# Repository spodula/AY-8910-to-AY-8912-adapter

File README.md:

# AY-8910-to-AY-8912-adapter
PCB to adapt an AY-3-8912 footprint to an AY-3-8910 chip

This project was done for my Superfo Harlequin 128 build because the cost of an AY-3-8912 is substantially more
than an AY-3-8910 despite the latter being much more functional. Even taking into account PCB manafacturing costs. 

If you want a PCB, The Gerber folder can just be zipped up and sent straight to your preferred PCB manafacturer.

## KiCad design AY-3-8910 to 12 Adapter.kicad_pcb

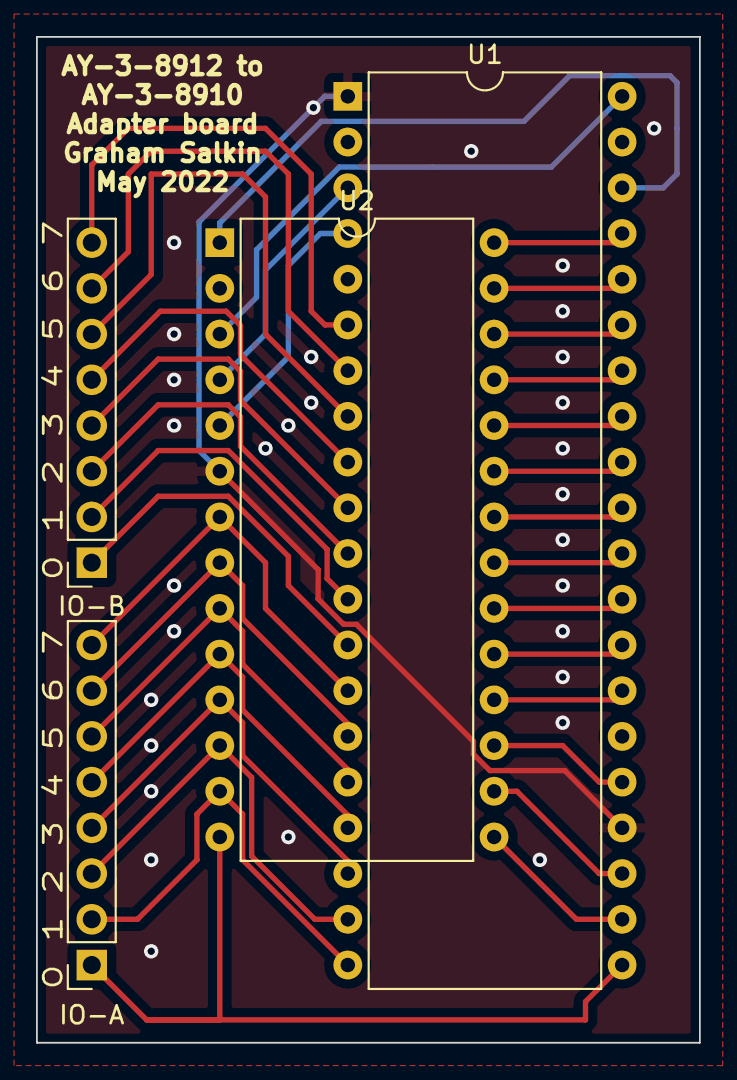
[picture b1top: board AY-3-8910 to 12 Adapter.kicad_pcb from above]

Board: 2 copper layers, 36.8 x 55.9 mm, 4 parts (0 on the bottom side), 35 nets.

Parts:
IO-A: 0 1 2 3 4 5 6 7; PinSocket_1x08_P2.54mm_Vertical
IO-B: 0 1 2 3 4 5 6 7; PinSocket_1x08_P2.54mm_Vertical
U1: AY-3-8910; DIP-40_W15.24mm
U2: AY-3-8912; DIP-28_W15.24mm

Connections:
GND: U1.1 (Vss), U1.24 (/A9), U2.6 (Vss)
unnamed: IO-B.1, U1.13 (IOB0)
unnamed: IO-B.2, U1.12 (IOB1)
unnamed: IO-B.3, U1.11 (IOB2)
unnamed: IO-B.4, U1.10 (IOB3)
unnamed: IO-B.5, U1.9 (IOB4)
unnamed: IO-B.6, U1.8 (IOB5)
unnamed: IO-B.7, U1.7 (IOB6)
unnamed: IO-B.8, U1.6 (IOB7)
unnamed: IO-A.1, U1.21 (IOA0), U2.14 (IOA0)
unnamed: IO-A.2, U1.20 (IOA1), U2.13 (IOA1)
unnamed: IO-A.3, U1.19 (IOA2), U2.12 (IOA2)
unnamed: IO-A.4, U1.18 (IOA3), U2.11 (IOA3)
unnamed: IO-A.5, U1.17 (IOA4), U2.10 (IOA4)
unnamed: IO-A.6, U1.16 (IOA5), U2.9 (IOA5)
unnamed: IO-A.7, U1.15 (IOA6), U2.8 (IOA6)
unnamed: IO-A.8, U1.14 (IOA7), U2.7 (IOA7)
unnamed: U1.3 (Analog_B), U2.4 (Analog_B)
unnamed: U1.4 (Analog_A), U2.5 (Analog_A)
unnamed: U1.22 (CLOCK), U2.15 (CLOCK)
unnamed: U1.23 (/RESET), U2.16 (/RESET)
unnamed: U1.25 (A8), U2.17 (A8)
unnamed: U1.27 (BDIR), U2.18 (BDIR)
unnamed: U1.28 (BC2), U2.19 (BC2)
unnamed: U1.29 (BC1), U2.20 (BC1)
unnamed: U1.30 (DA7), U2.21 (DA7)
unnamed: U1.31 (DA6), U2.22 (DA6)
unnamed: U1.32 (DA5), U2.23 (DA5)
unnamed: U1.33 (DA4), U2.24 (DA4)
unnamed: U1.34 (DA3), U2.25 (DA3)
unnamed: U1.35 (DA2), U2.26 (DA2)
unnamed: U1.36 (DA1), U2.27 (DA1)
unnamed: U1.37 (DA0), U2.28 (DA0)
unnamed: U1.38 (Analog_C), U2.1 (Analog_C)
unnamed: U1.40 (Vcc), U2.3 (Vcc)

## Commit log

2022-05-25 Added AY symbol library for completeness
2022-05-25 Fixed schematic placement
2022-05-25 Removed bad file from root
2022-05-25 Placed the schematic in its proper place
